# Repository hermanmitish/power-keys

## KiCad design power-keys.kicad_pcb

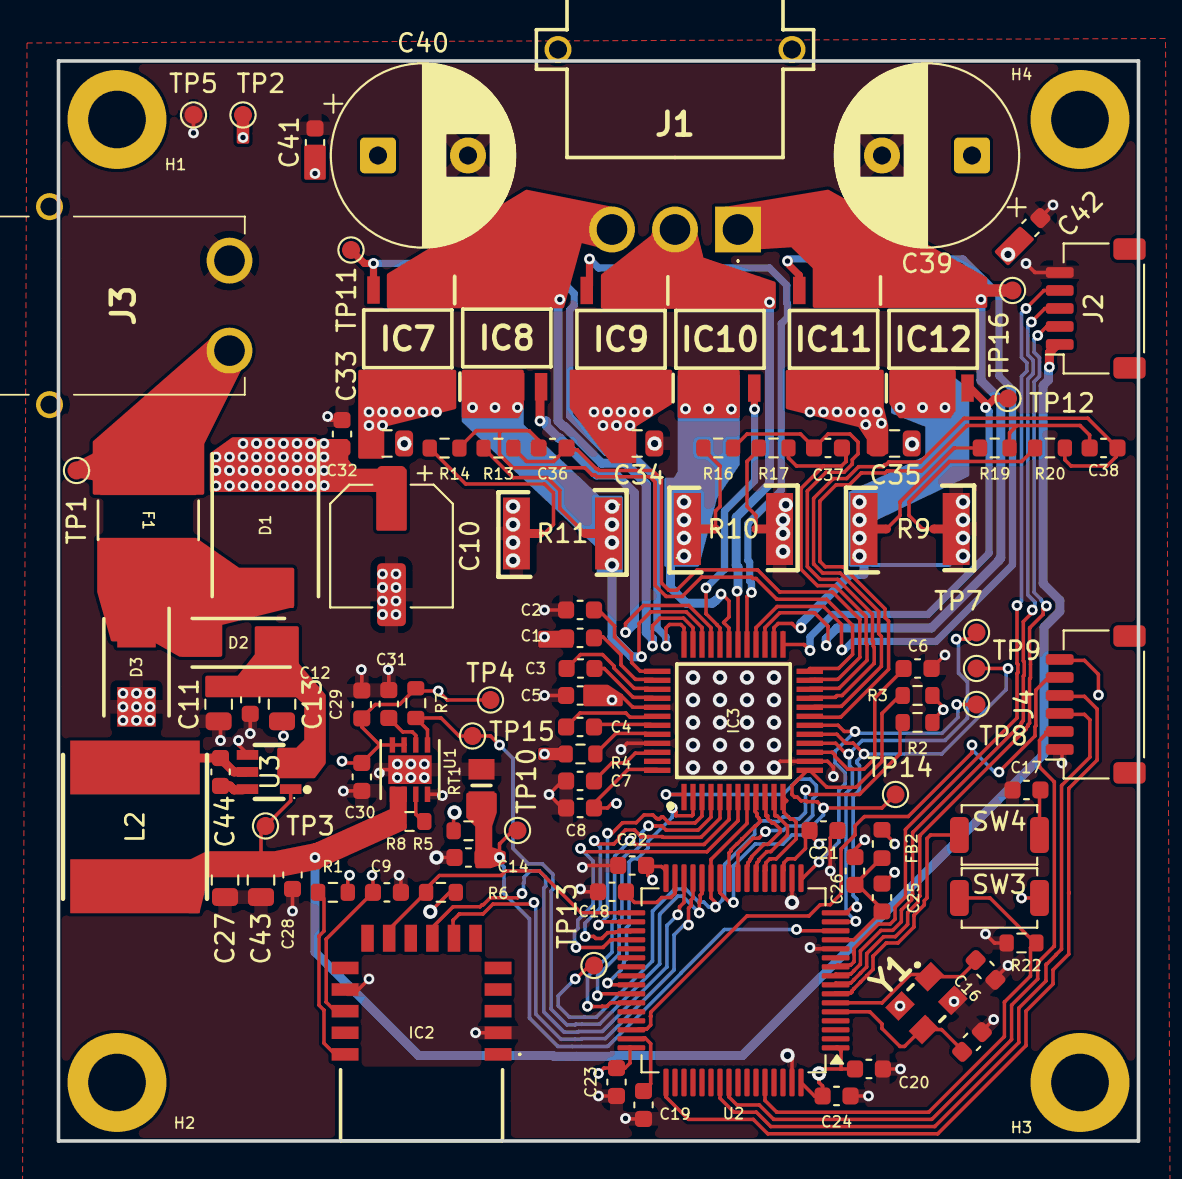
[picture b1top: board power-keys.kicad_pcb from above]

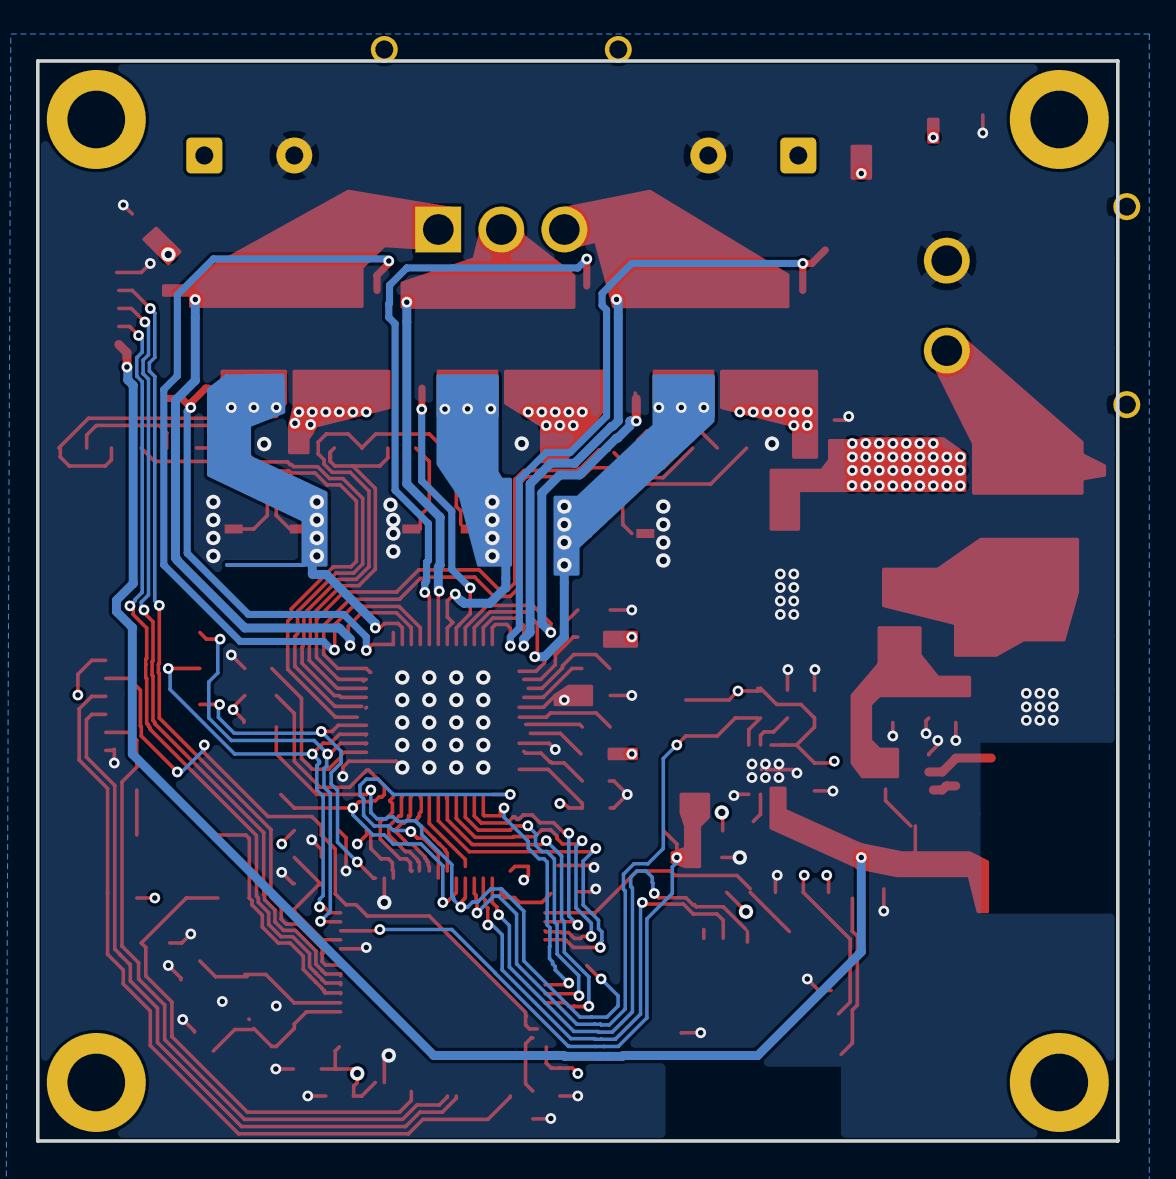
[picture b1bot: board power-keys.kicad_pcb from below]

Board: 4 copper layers, 60.0 x 60.0 mm, 118 parts (6 on the bottom side), 87 nets.

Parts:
C1, C7, C8, C29: 1u; C_0603_1608Metric
C2, C18, C19: 2.2u; C_0603_1608Metric
C3, C4: 0.047u; C_0603_1608Metric
C5, C28: 4.7u; C_0603_1608Metric
C6: 1n; C_0603_1608Metric
C9, C26: 10u; C_0603_1608Metric
C10: 100u 35V; CP_Elec_6.3x7.7
C11, C13: 10u 25V; C_0805_2012Metric
C12, C14, C17, C20, C21, C22, C23, C24, C25, C30, C32, C44: 100n; C_0603_1608Metric
C15, C16: 22pF; C_0603_1608Metric
C27, C43: 22u 10V; C_0805_2012Metric
C31, C36, C37, C38: 1000p; C_0603_1608Metric
C33, C34, C35: 1u; C_0805_2012Metric
C39, C40: 470u 35V; CP_Radial_D10.0mm_P5.00mm
C41, C42: 0.1u; C_0603_1608Metric
D1: SK54; DIOM7959X262N
D2: SS14; DIOM5127X261N
D3: SMBJ18A; DIOM5436X244N
F1: 2920L500/16MR; FUSE_2920L500&slash_16_LTF
FB2: 600ohm/200mA; L_0603_1608Metric
H1, H2, H3, H4: MountingHole; MountingHole_3.2mm_M3_ISO14580_Pad
IC2: RN4871-I_RM140; RN4871IRM140
IC3: DRV8305NPHPR; QFP50P900X900X120-48N
IC7, IC8, IC9, IC10, IC11, IC12: FDS4080N7; SOIC127P600X175-8N
J1: Motor Connector; MR30PWM
J2: Hall Sensor Conn_01x05; JST_SH_SM05B-SRSS-TB_1x05-1MP_P1.00mm_Horizontal
J3: XT30PW-M; XT30PWM
J4: Conn_ARM_JTAG_SWD_10; JST_SH_SM06B-SRSS-TB_1x06-1MP_P1.00mm_Horizontal
L2: 4.7uH 2A; IND-SMD_L8.0-W8.0_ASPI-8040S
NT1, NT2, NT3, NT4, NT5, NT6, NT7, NT8, NT9, NT10, NT11, NT12: NetTie_2; NetTie-2_SMD_Pad0.5mm
R1, R2, R3, R6, R8, R22: 10k; R_0603_1608Metric
R4: 100; R_0603_1608Metric
R5: 2K7; R_0603_1608Metric
R7: 100k; R_0603_1608Metric
R9, R10, R11: 7m5 3W; RES-SMD_L6.3-W3.2_CSSH2512
R13, R14, R16, R17, R19, R20: 100R; R_0603_1608Metric
RT1: B57421V2103J062; THRMC2012X130N
SW3, SW4: SW_Push; SW_SPST_TS-1088-xR020
TP1, TP2, TP3, TP4, TP5, TP7, TP8, TP9, TP10, TP11, TP12, TP13, TP14, TP15, TP16: TestPoint; TestPoint_Pad_D1.0mm
U1: MCP1727-3302E/MF; DFN8_3x3MC_MCH
U2: STM32F405RGTx; LQFP-64_10x10mm_P0.5mm
U3: AP63205WU-7; TSOT-23-6_L2.9-W1.6-P0.95-LS2.8-BL
Y1: ABM8-25.000MHZ-B2-T; ABM810000MHZ12D2W

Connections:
+3V3: C8.2, C9.1, C20.2, C21.2, C22.2, C23.2, C24.2, C29.1, C30.1, FB2.1, IC2.14 (VBAT), IC3.48 (VREG), J4.6, R1.2, R2.1, R3.1, R5.1, R6.2, R7.1, SW3.1, TP4.1 (1_1), U1.7, U1.8, U2.1 (VBAT), U2.19 (VDD), U2.32 (VDD), U2.48 (VDD), U2.64 (VDD)
+3V3A: C25.1, C26.1, FB2.2, U2.13 (VDDA)
+5V: C27.1, C28.1, C43.1, J2.1, L2.2, R8.1, TP3.1 (1_1), U1.1, U1.2, U3.1 (FB)
+12M: C2.1, C5.2, C10.1, C32.1, C33.1, C34.1, C35.1, C39.1, C40.1, C41.1, C42.1, D1.1 (K), IC3.41 (PVDD), IC7.5 (D_1), IC7.6 (D_2), IC7.7 (D_3), IC7.8 (D_4), IC9.5 (D_1), IC9.6 (D_2), IC9.7 (D_3), IC9.8 (D_4), IC11.5 (D_1), IC11.6 (D_2), IC11.7 (D_3), IC11.8 (D_4), R4.2, TP2.1 (1_1)
+12_FUSED: D1.2 (A), D2.2 (A), D3.1 (K), F1.2
+12_IN: F1.1, J3.1, TP1.1 (1_1)
/Bluetooth/BT_RST: IC2.10 (RST_N), R6.1, U2.33 (PB12)
/Bluetooth/BT_RX: IC2.7 (UART_RX), U2.29 (PB10)
/Bluetooth/BT_TX: IC2.8 (UART_TX), U2.30 (PB11)
/MCU/EN_GATE: IC3.1 (EN_GATE), U2.24 (PC4)
/MCU/INHA: IC3.2 (INHA), U2.41 (PA8)
/MCU/INHB: IC3.4 (INHB), U2.42 (PA9)
/MCU/INHC: IC3.6 (INHC), U2.43 (PA10)
/MCU/INLA: IC3.3 (INLA), U2.34 (PB13)
/MCU/INLB: IC3.5 (INLB), U2.35 (PB14)
/MCU/INLC: IC3.7 (INLC), U2.36 (PB15)
/MCU/LDO_PWRGD: R7.2, TP15.1 (1_1), U1.5, U2.28 (PB2)
/MCU/NFAULT: IC3.8 (NFAULT), R2.2, TP13.1 (1_1), U2.27 (PB1)
/MCU/NSCS: IC3.9 (NSCS), U2.25 (PC5)
/MCU/PWRGD: IC3.13 (PWRGD), R3.2, TP14.1 (1_1), U2.26 (PB0)
/MCU/SCLK: IC3.12 (SCLK), U2.21 (PA5)
/MCU/SDI: IC3.10 (SDI), U2.23 (PA7)
/MCU/SDO: IC3.11 (SDO), U2.22 (PA6)
/MCU/SOA: IC3.16 (SO1), TP7.1 (1_1), U2.15 (PA1)
/MCU/SOB: IC3.17 (SO2), TP9.1 (1_1), U2.16 (PA2)
/MCU/SOC: IC3.18 (SO3), TP8.1 (1_1), U2.17 (PA3)
/MCU/TEMP1: C14.1, R5.2, RT1.1, TP10.1 (1_1), U2.14 (PA0)
/Motor Driver/GHA: IC3.36 (GHA), IC7.4 (G), TP11.1 (1_1)
/Motor Driver/GHB: IC3.29 (GHB), IC9.4 (G)
/Motor Driver/GHC: IC3.28 (GHC), IC11.4 (G)
/Motor Driver/GLA: IC3.33 (GLA), IC8.4 (G)
/Motor Driver/GLB: IC3.32 (GLB), IC10.4 (G)
/Motor Driver/GLC: IC3.25 (GLC), IC12.4 (G), TP12.1 (1_1)
/Motor Driver/SHA: IC3.35 (SHA), NT7.1
/Motor Driver/SHB: IC3.30 (SHB), NT8.1
/Motor Driver/SHC: IC3.27 (SHC), NT9.1
/Motor Driver/SLA: IC3.34 (SLA), NT10.1
/Motor Driver/SLB: IC3.31 (SLB), NT11.1
/Motor Driver/SLC: IC3.26 (SLC), NT12.1
/Motor Driver/SN_HA: C36.1, IC3.23 (SN1), R13.1
/Motor Driver/SN_HB: C37.1, IC3.21 (SN2), R16.1
/Motor Driver/SN_HC: C38.1, IC3.19 (SN3), R19.1
/Motor Driver/SN_LA: C36.2, IC3.24 (SP1), R14.1
/Motor Driver/SN_LB: C37.2, IC3.22 (SP2), R17.1
/Motor Driver/SN_LC: C38.2, IC3.20 (SP3), R20.1
/Power Keys/PHASE_A: IC7.1 (S_1), IC7.2 (S_2), IC7.3 (S_3), IC8.5 (D_1), IC8.6 (D_2), IC8.7 (D_3), IC8.8 (D_4), J1.3, NT7.2
/Power Keys/PHASE_B: IC9.1 (S_1), IC9.2 (S_2), IC9.3 (S_3), IC10.5 (D_1), IC10.6 (D_2), IC10.7 (D_3), IC10.8 (D_4), J1.2, NT8.2
/Power Keys/PHASE_C: IC11.1 (S_1), IC11.2 (S_2), IC11.3 (S_3), IC12.5 (D_1), IC12.6 (D_2), IC12.7 (D_3), IC12.8 (D_4), J1.1, NT9.2, TP16.1 (1_1)
GND: C1.2, C5.1, C6.1, C7.1, C8.1, C9.2, C10.2, C11.2, C12.2, C13.2, C14.2, C15.1, C16.1, C17.1, C18.1, C19.1, C20.1, C21.1, C22.1, C23.1, C24.1, C25.2, C26.2, C27.2, C28.2, C29.2, C30.2, C31.2, C32.2, C33.2, C34.2, C35.2, C39.2, C40.2, C41.2, C42.2, C43.2, D3.2 (A), IC2.2 (GND_1), IC2.13 (GND_2), IC3.14 (GND_1), IC3.45 (GND_2), J2.5, J3.2, J3.3, J3.4, J4.1, NT2.2, NT4.2, NT6.2, R9.2, R10.2, R11.2, R22.1, RT1.2, TP5.1 (1_1), U1.4, U1.9, U2.12 (VSSA), U2.18 (VSS), U2.63 (VSS), U3.4 (GND), Y1.2 (GND_1), Y1.4 (GND_2)
unnamed: C17.2, SW4.1
unnamed: C31.1, U1.6
unnamed: C11.1, C12.1, C13.1, D2.1 (K), U3.2 (EN), U3.3 (VIN)
unnamed: IC2.16 (P2_0), R1.1
unnamed: C6.2, IC3.15 (AVDD)
unnamed: C4.1, IC3.43 (CP1H)
unnamed: C4.2, IC3.42 (CP1L)
unnamed: C3.2, IC3.39 (CP2H)
unnamed: C3.1, IC3.40 (CP2L)
unnamed: C7.2, IC3.46 (DVDD)
unnamed: C2.2, IC3.38 (VCPH)
unnamed: C1.1, IC3.37 (VCP_LSD)
unnamed: IC3.44 (VDRAIN), R4.1
unnamed: IC8.1 (S_1), IC8.2 (S_2), IC8.3 (S_3), NT3.2, NT10.2, R11.1
unnamed: IC10.1 (S_1), IC10.2 (S_2), IC10.3 (S_3), NT1.2, NT11.2, R10.1
unnamed: IC12.1 (S_1), IC12.2 (S_2), IC12.3 (S_3), NT5.2, NT12.2, R9.1
unnamed: J2.2, U2.8 (PC0)
unnamed: J2.3, U2.9 (PC1)
unnamed: J2.4, U2.10 (PC2)
unnamed: J4.2, U2.56 (PB4)
unnamed: J4.3, U2.55 (PB3)
unnamed: J4.4, U2.49 (PA14)
unnamed: J4.5, U2.46 (PA13)
unnamed: NT1.1, R16.2
unnamed: NT2.1, R17.2
unnamed: NT3.1, R13.2
unnamed: NT4.1, R14.2
unnamed: NT5.1, R19.2
unnamed: NT6.1, R20.2
unnamed: R8.2, U1.3
unnamed: R22.2, SW3.2, U2.60 (BOOT0)
unnamed: SW4.2, U2.7 (NRST)
unnamed: C15.2, U2.5 (PH0), Y1.3 (X2)
unnamed: C16.2, U2.6 (PH1), Y1.1 (X1)
unnamed: C18.2, U2.31 (VCAP_1)
unnamed: C19.2, U2.47 (VCAP_2)
unnamed: C44.1, U3.6 (BST)
unnamed: C44.2, L2.1, U3.5 (SW)

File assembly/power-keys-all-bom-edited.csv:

Designator,Comment,Footprint
"C1,C7,C8,C29",1u,Capacitor_SMD:C_0603_1608Metric
"C2,C18,C19",2.2u,Capacitor_SMD:C_0603_1608Metric
"C3,C4",0.047u,Capacitor_SMD:C_0603_1608Metric
"C5,C28",4.7u,Capacitor_SMD:C_0603_1608Metric
C6,1n,Capacitor_SMD:C_0603_1608Metric
"C9,C11,C26",10u,Capacitor_SMD:C_0603_1608Metric
"C10,C13",100u,Capacitor_SMD:C_0603_1608Metric
"C12,C14,C17,C20,C21,C22,C23,C24,C25,C30,C32",100n,Capacitor_SMD:C_0603_1608Metric
"C15,C16",22pF,Capacitor_SMD:C_0603_1608Metric
C27,1000u,Capacitor_SMD:C_0603_1608Metric
"C31,C36,C37,C38",1000p,Capacitor_SMD:C_0603_1608Metric
"C33,C34,C35",1u,Capacitor_SMD:C_0805_2012Metric
"C39,C40",470u,Capacitor_THT:CP_Radial_D10.0mm_P5.00mm
"C41,C42",0.1u,Capacitor_SMD:C_0603_1608Metric
D1,SK54,project:DIOM7959X262N
D2,SS14,project:DIOM5127X261N
D3,SMBJ18A,project:DIOM5436X244N
D4,JANTX1N5822US,project:DIOMELF5436N
F1,2920L500/16MR,project:FUSE_2920L500&slash_16_LTF
FB2,600ohm/200mA,Inductor_SMD:L_0603_1608Metric
IC2,RN4871-I_RM140,project:RN4871IRM140
IC3,DRV8305NPHPR,project:QFP50P900X900X120-48N
"IC7,IC8,IC9,IC10,IC11,IC12",SI4122DY-T1-GE3,SOIC127P600X175-8N
J1,Motor Connector,TerminalBlock_Phoenix:TerminalBlock_Phoenix_MKDS-3-3-5.08_1x03_P5.08mm_Horizontal
J2,Hall Sensor Conn_01x05,Connector_JST:JST_SH_BM05B-SRSS-TB_1x05-1MP_P1.00mm_Vertical
J3,XT30PW-M,XT30PWM
J4,Conn_ARM_JTAG_SWD_10,Connector_JST:JST_SH_BM06B-SRSS-TB_1x06-1MP_P1.00mm_Vertical
L1,100uH,Diode_SMD:D_MELF
"R1,R2,R3,R6,R8,R22",10k,Resistor_SMD:R_0603_1608Metric
R4,100,Resistor_SMD:R_0603_1608Metric
R5,2K7,Resistor_SMD:R_0603_1608Metric
R7,100k,Resistor_SMD:R_0603_1608Metric
"R9,R10,R11",7m5,project:RESM11569X253N
"R13,R14,R16,R17,R19,R20",100R,Resistor_SMD:R_0603_1608Metric
RT1,B57421V2103J062,project:THRMC2012X130N
"SW3,SW4",SW_Push,Button_Switch_SMD:SW_SPST_TS-1088-xR020
U1,MCP1727-3302E/MF,project:DFN8_3x3MC_MCH
U2,STM32F405RGTx,Package_QFP:LQFP-64_10x10mm_P0.5mm
U3,LM2576D2TR4-5G,project:D2TSUFFIX-CASE936A-02-ISSUEC
Y1,ABM8-25.000MHZ-B2-T,ABM810000MHZ12D2W
